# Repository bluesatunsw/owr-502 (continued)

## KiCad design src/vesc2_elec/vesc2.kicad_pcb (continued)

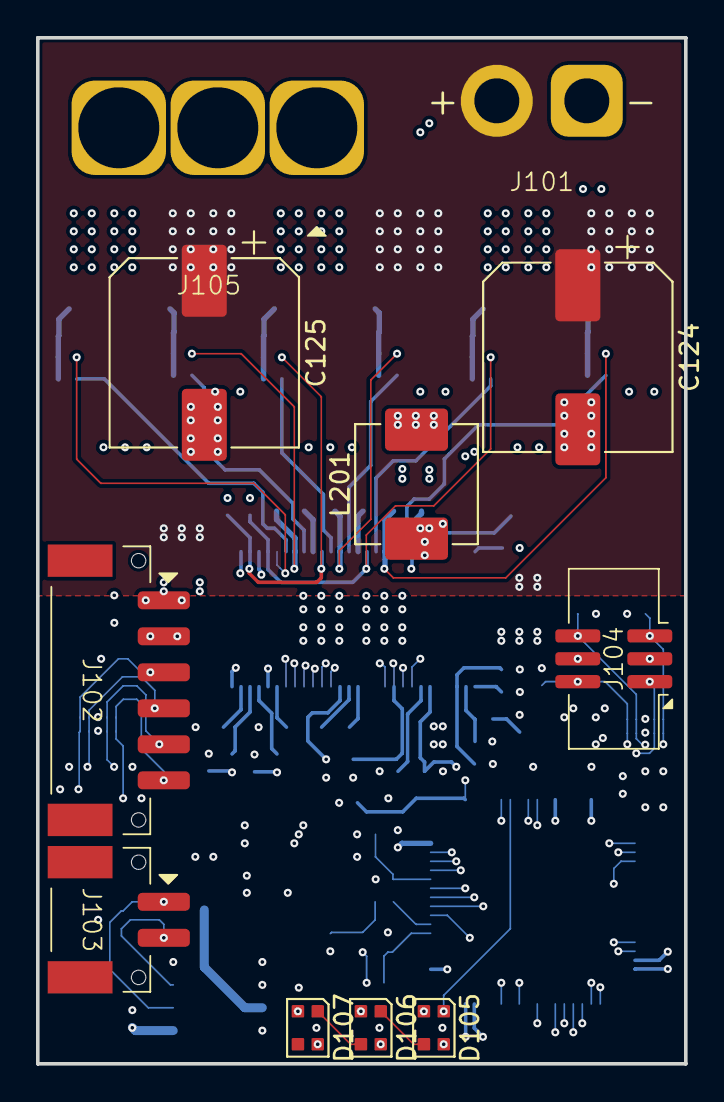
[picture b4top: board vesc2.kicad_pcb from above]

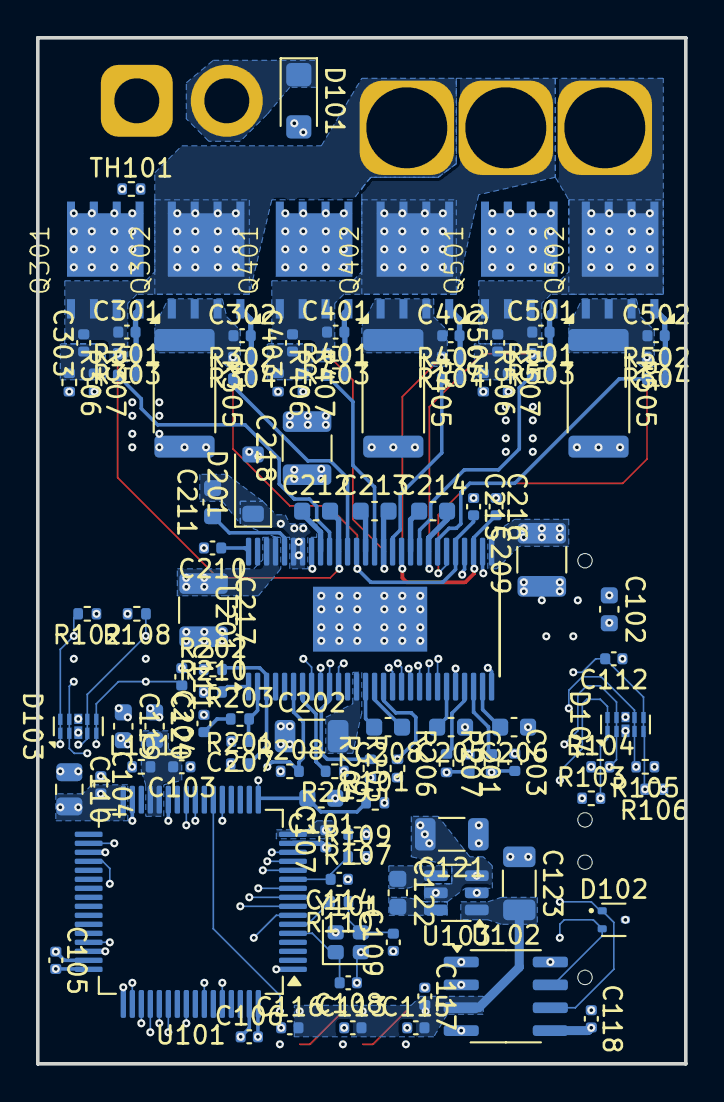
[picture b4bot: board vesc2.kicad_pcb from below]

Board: 6 copper layers, 36.0 x 57.0 mm, 120 parts (109 on the bottom side), 80 nets.

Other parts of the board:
D102: DTVS; SOT-523

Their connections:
/CANH: D102.2; also elsewhere on the board
/CANL: D102.1; also elsewhere on the board
GND: D102.3; also elsewhere on the board

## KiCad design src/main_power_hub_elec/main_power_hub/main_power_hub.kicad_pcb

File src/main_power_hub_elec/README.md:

# Main Power Hub (MPH)

A device which monitors and distributes battery power onto four subcircuits (intended to be either computing power hubs or subsystem power hubs). It complies with the common device specification 2025-04.

Power input from the battery is provided via a male XT90 connector and each of the subcircuits has a female XT60 power output connector.

## Switching
Power to each of the subcircuits can be toggled by the MCU. Triggering the estop, a normally closed contact wired to the device, removes power from all subcircuits bypassing the control of the MCU. The MCU is always powered. As implied by the connector name, each channel is able to output 60A peak and 40A continuous.

Switching on ramps slowly (soft pullup resistor + gate capacitance), switching off is instantaneous.

Power MOSFET: C2902884
https://www.lcsc.com/datasheet/C2902884.pdf

BJT on pullup: BC846s
https://diotec.com/request/datasheet/bc846s.pdf

Gate drive voltage is provided by a charge pump circuit that sums the battery voltage + the 12V rail.
The gate driver is a simple BJT pullup configuration.

Charge pump MOSFET: SSM3K333R
https://toshiba.semicon-storage.com/info/SSM3K333R_datasheet_en_20250220.pdf?did=6736&prodName=SSM3K333R

## Monitoring
The bus voltage is monitored through a voltage divider into an ADC (10k / (10k + 220k)).
The output current of each channel is monitored.
This is done with a 1m shunt resistor on each channel.
The voltage across the resistor is fed into one internal STM32 op-amp per channel.
A compensation capacitor is placed on the output of each op-amp to introduce a pole near 1kHz.
The op-amp pins should be connected internally to the ADCs using software.

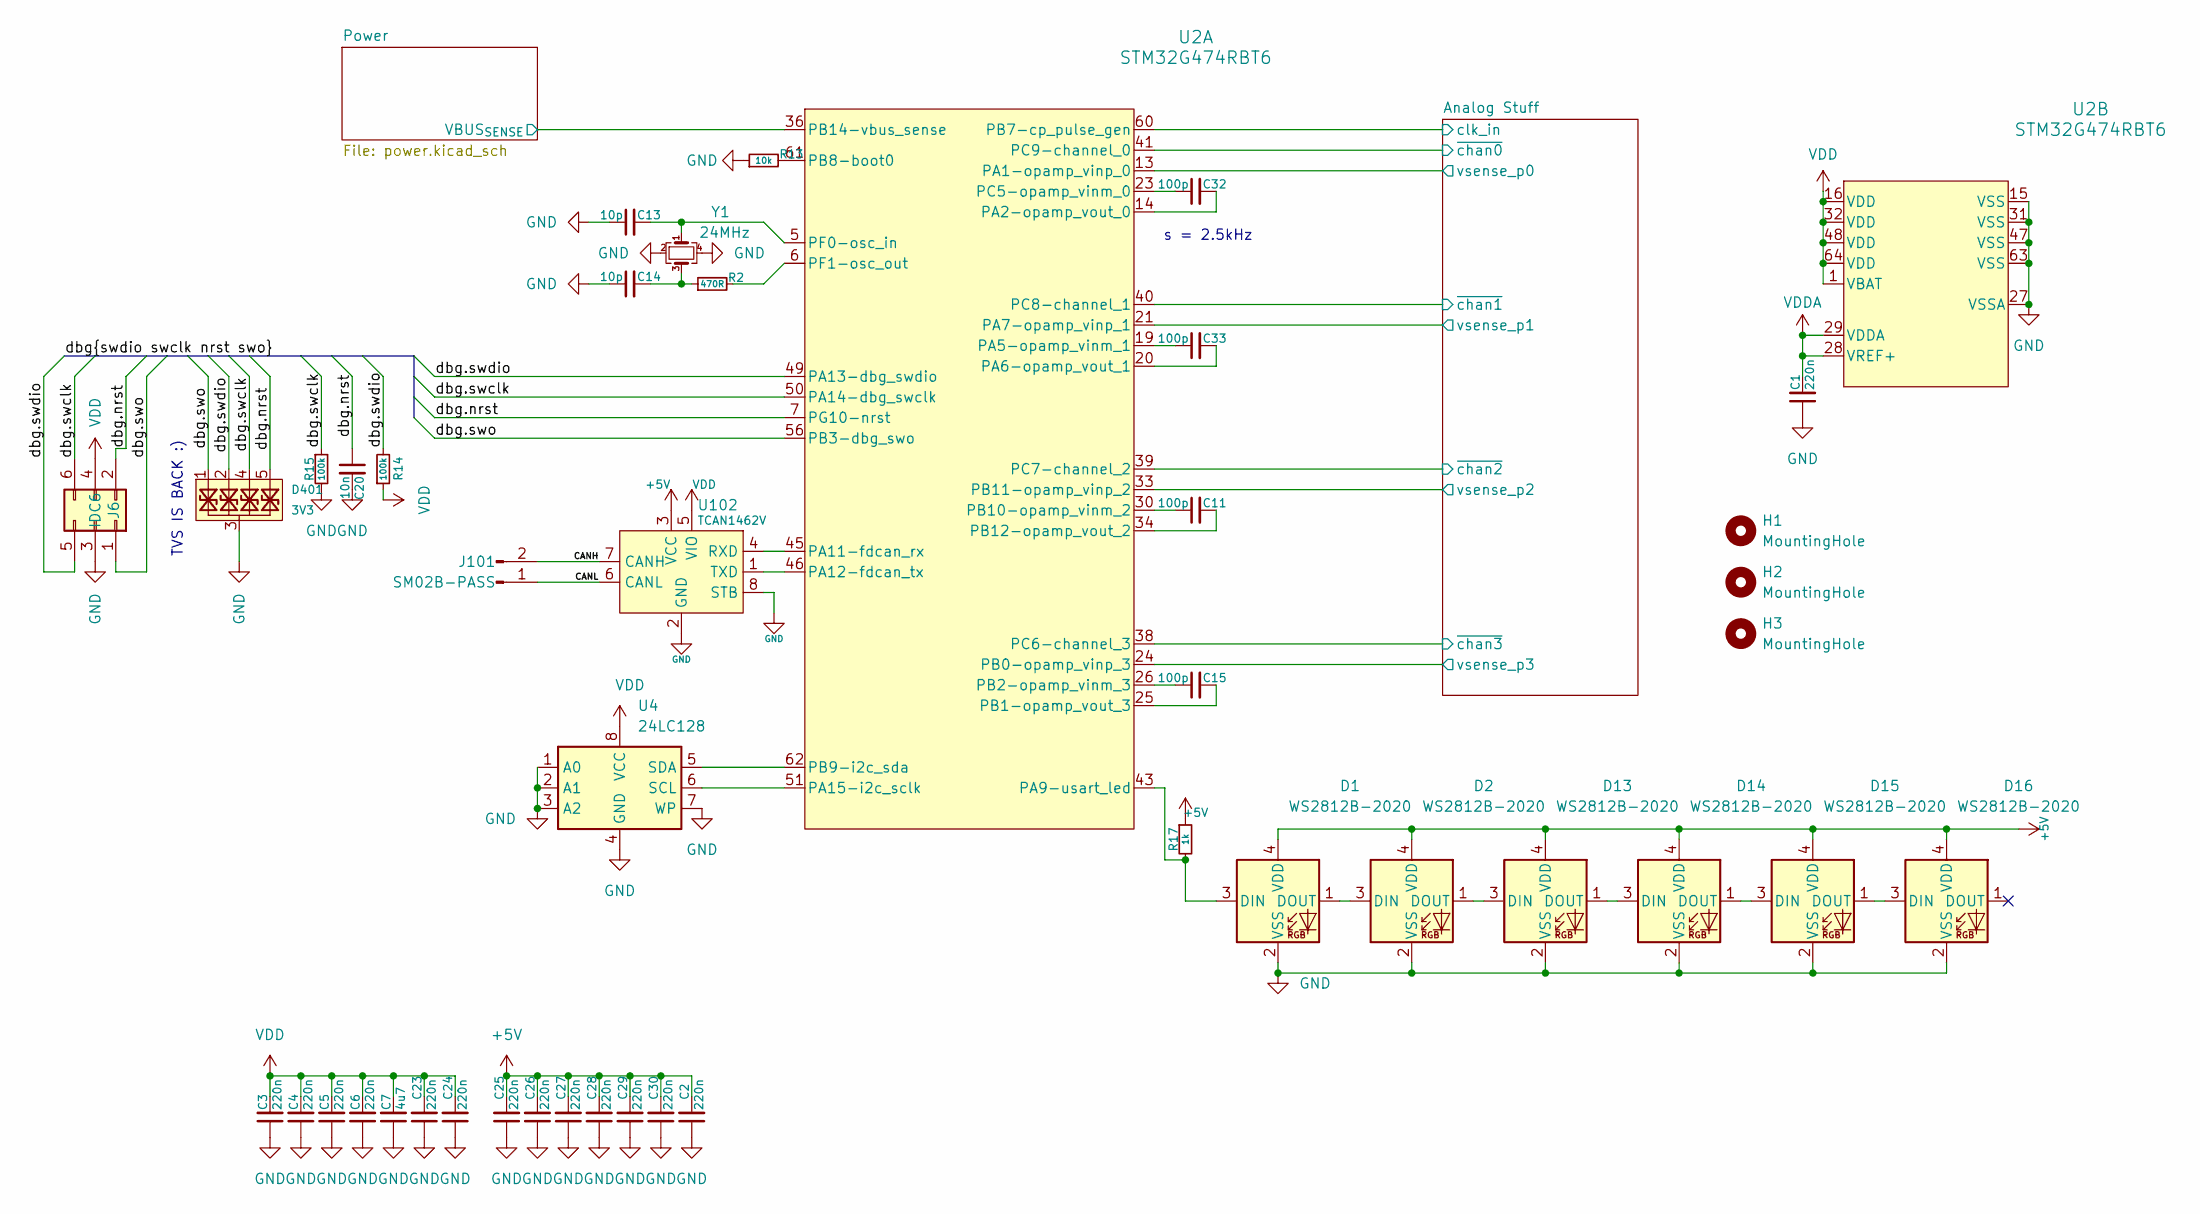
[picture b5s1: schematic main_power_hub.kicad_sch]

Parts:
C1, C2, C3, C4, C5, C6, C23, C24, C25, C26, C27, C28, C29, C30: 220n; C_0402_1005Metric
C7: 4u7; C_0805_2012Metric
C11, C15, C32, C33: 100p; C_0402_1005Metric
C13, C14: 10p; C_0402_1005Metric
C20: 10n; C_0402_1005Metric
D1, D2, D13, D14, D15, D16: WS2812B-2020
D401: 3V3; Diodes_UDFN-10_1x2.5mm_P0.5mm
H1, H2, H3: MountingHole; M2.5_Internal
J6: IDC6
J101: SM02B-PASS
R2: 470R; R_0402_1005Metric
R13: 10k; R_0402_1005Metric
R14, R15: 100k; R_0402_1005Metric
R17: 1k; R_0402_1005Metric
U2: STM32G474RBT6; LQFP-64-0.5
U4: 24LC128; TSSOP-8_4.4x3.0-0.65
U102: TCAN1462V; SOIC-8_3.9x4.9mm_P1.27mm
Y1: 24MHz; Crystal_SMD_2016-4Pin_2.0x1.6mm

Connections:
+5V: C2.2, C25.2, C26.2, C27.2, C28.2, C29.2, C30.2, D1.4 (VDD), D2.4 (VDD), D13.4 (VDD), D14.4 (VDD), D15.4 (VDD), D16.4 (VDD), R17.1, U102.3 (VCC); also elsewhere on the board
/Analog Stuff/clk_in: U2.60 (PB7-cp_pulse_gen); also elsewhere on the board
/Analog Stuff/vsense_p0: U2.13 (PA1-opamp_vinp_0); also elsewhere on the board
/Analog Stuff/vsense_p1: U2.21 (PA7-opamp_vinp_1); also elsewhere on the board
/Analog Stuff/vsense_p2: U2.33 (PB11-opamp_vinp_2); also elsewhere on the board
/Analog Stuff/vsense_p3: U2.24 (PB0-opamp_vinp_3); also elsewhere on the board
/Analog Stuff/~chan0: U2.41 (PC9-channel_0); also elsewhere on the board
/Analog Stuff/~chan1: U2.40 (PC8-channel_1); also elsewhere on the board
/Analog Stuff/~chan2: U2.39 (PC7-channel_2); also elsewhere on the board
/Analog Stuff/~chan3: U2.38 (PC6-channel_3); also elsewhere on the board
/CANH: J101.2, U102.7 (CANH); also elsewhere on the board
/CANL: J101.1, U102.6 (CANL); also elsewhere on the board
/Power/VBUS_{SENSE}: U2.36 (PB14-vbus_sense); also elsewhere on the board
/dbg.nrst: C20.1, D401.5, D401.6, J6.2, U2.7 (PG10-nrst)
/dbg.swclk: D401.4, D401.7, J6.6, R15.1, U2.50 (PA14-dbg_swclk)
/dbg.swdio: D401.2, D401.9, J6.5, R14.2, U2.49 (PA13-dbg_swdio)
/dbg.swo: D401.1, D401.10, J6.1, U2.56 (PB3-dbg_swo)
unnamed: C14.2, R2.1, Y1.3
unnamed: D1.3 (DIN), R17.2, U2.43 (PA9-usart_led)
unnamed: D1.1 (DOUT), D2.3 (DIN)
unnamed: D2.1 (DOUT), D13.3 (DIN)
unnamed: D13.1 (DOUT), D14.3 (DIN)
unnamed: D14.1 (DOUT), D15.3 (DIN)
unnamed: D15.1 (DOUT), D16.3 (DIN)
unnamed: C32.2, U2.14 (PA2-opamp_vout_0)
unnamed: C33.1, U2.19 (PA5-opamp_vinm_1)
unnamed: C33.2, U2.20 (PA6-opamp_vout_1)
unnamed: U2.51 (PA15-i2c_sclk), U4.6 (SCL)
unnamed: C15.2, U2.25 (PB1-opamp_vout_3)
unnamed: C15.1, U2.26 (PB2-opamp_vinm_3)
unnamed: R13.2, U2.61 (PB8-boot0)
unnamed: U2.62 (PB9-i2c_sda), U4.5 (SDA)
unnamed: C11.1, U2.30 (PB10-opamp_vinm_2)
unnamed: C11.2, U2.34 (PB12-opamp_vout_2)
unnamed: C32.1, U2.23 (PC5-opamp_vinm_0)
unnamed: C13.2, U2.5 (PF0-osc_in), Y1.1
unnamed: R2.2, U2.6 (PF1-osc_out)
unnamed: U2.45 (PA11-fdcan_rx), U102.4 (RXD)
unnamed: U2.46 (PA12-fdcan_tx), U102.1 (TXD)
VDD: C3.2, C4.2, C5.2, C6.2, C7.2, C23.2, C24.2, J6.4, R14.1, U2.1 (VBAT), U2.16 (VDD), U2.32 (VDD), U2.48 (VDD), U2.64 (VDD), U4.8 (VCC), U102.5 (VIO); also elsewhere on the board
VDDA: C1.2, U2.28 (VREF+), U2.29 (VDDA); also elsewhere on the board

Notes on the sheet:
s = 2.5kHz
TVS IS BACK :)

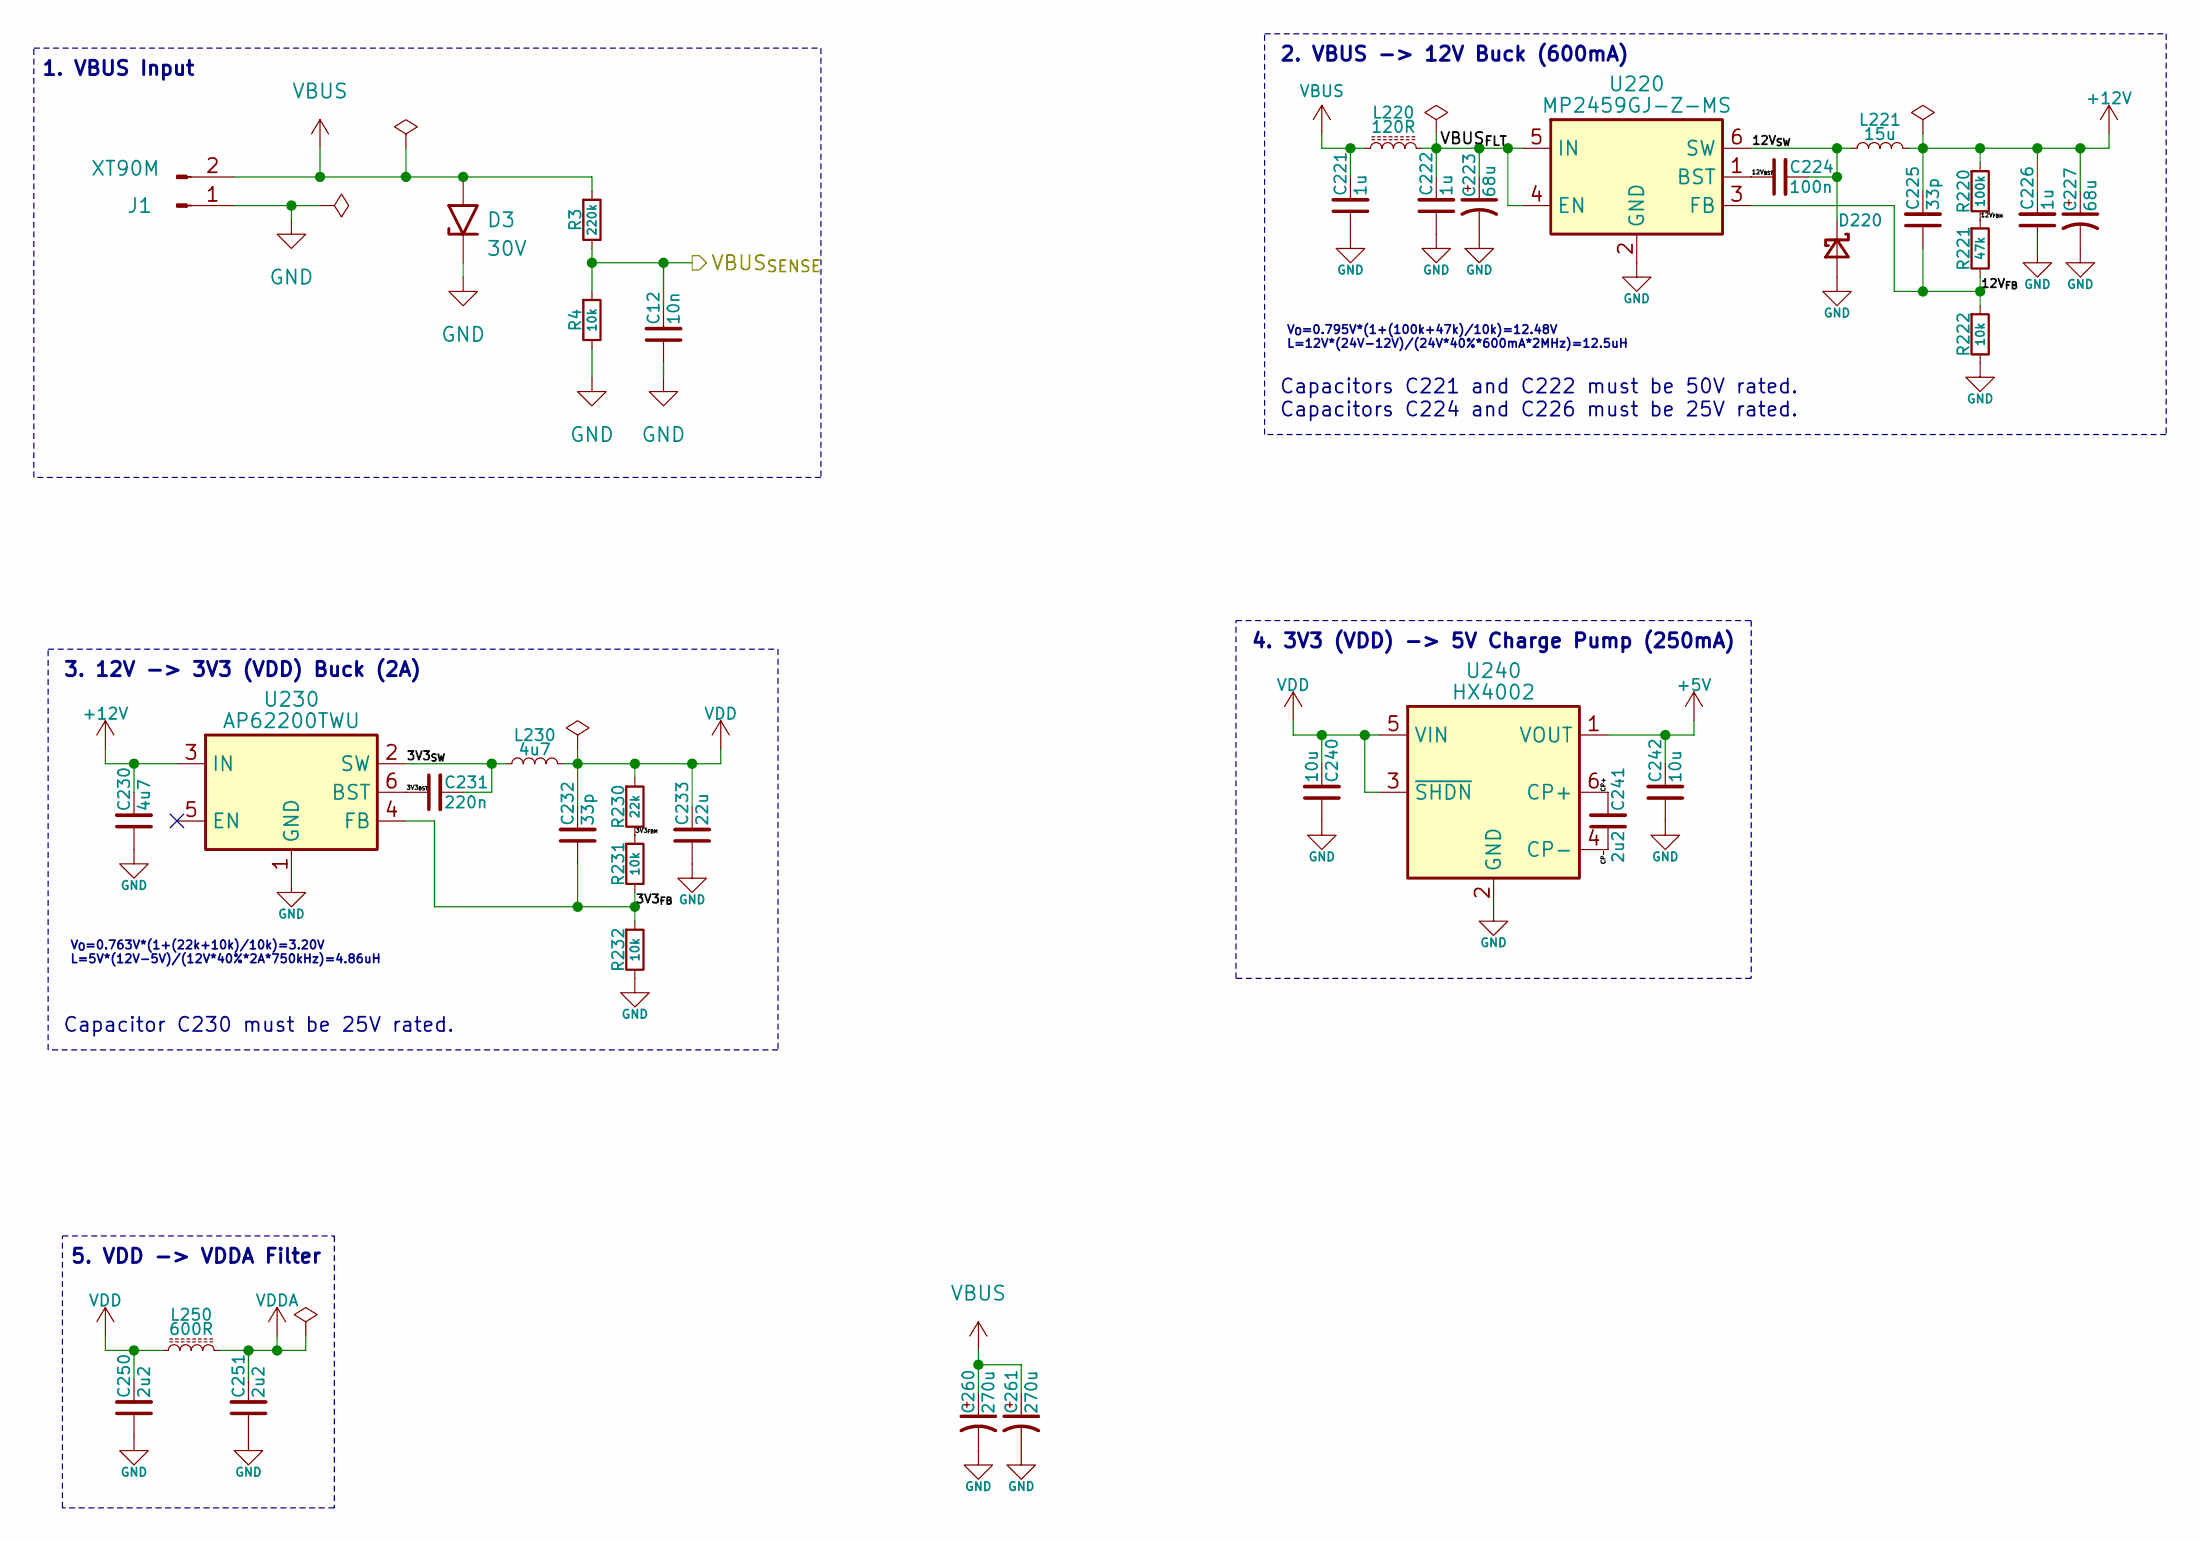
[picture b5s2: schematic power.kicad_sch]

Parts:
C12: 10n; C_0402_1005Metric
C221, C222: 1u; C_1206_3216Metric
C223, C227: 68u; CP_Elec_6.3x7.7
C224: 100n; C_0402_1005Metric
C225, C232: 33p; C_0402_1005Metric
C226: 1u; C_0805_2012Metric
C230: 4u7; C_1206_3216Metric
C231: 220n; C_0402_1005Metric
C233: 22u; C_1210_3225Metric
C240, C242: 10u; C_1206_3216Metric
C241, C250, C251: 2u2; C_0603_1608Metric
C260, C261: 270u; CP_Elec_10x10
D3: 30V; D_SMF
D220: D_Schottky_Small; D_SOD-123
J1: XT90M; AMASS_XT90PW-M_1x02_P10.90mm_Horizontal
L220: 120R; R_0603_1608Metric
L221: 15u; L_Changjiang_FNR5040S
L230: 4u7; L_Changjiang_FNR4020S
L250: 600R; R_0402_1005Metric
R3: 220k; R_0402_1005Metric
R4, R222, R231, R232: 10k; R_0402_1005Metric
R220: 100k; R_0402_1005Metric
R221: 47k; R_0402_1005Metric
R230: 22k; R_0402_1005Metric
U220: MP2459GJ-Z-MS; TSOT-23-6
U230: AP62200TWU; TSOT-23-6
U240: HX4002; SOT-23-6

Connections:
+5V: C242.2, U240.1 (VOUT); also elsewhere on the board
+12V: C225.2, C226.2, C227.1, C230.2, L221.1, R220.1, U230.3 (IN); also elsewhere on the board
/Power/3V3_{BST}: C231.1, U230.6 (BST)
/Power/3V3_{FBM}: R230.2, R231.1
/Power/3V3_{FB}: C232.1, R231.2, R232.1, U230.4 (FB)
/Power/3V3_{SW}: C231.2, L230.1, U230.2 (SW)
/Power/12V_{BST}: C224.1, U220.1 (BST)
/Power/12V_{FBM}: R220.2, R221.1
/Power/12V_{FB}: C225.1, R221.2, R222.1, U220.3 (FB)
/Power/12V_{SW}: C224.2, D220.1 (K), L221.2, U220.6 (SW)
/Power/CP+: C241.2, U240.6 (CP+)
/Power/CP-: C241.1, U240.4 (CP-)
/Power/VBUS_{FLT}: C222.2, C223.1, L220.2, U220.4 (EN), U220.5 (IN)
/Power/VBUS_{SENSE}: C12.2, R3.2, R4.1; also elsewhere on the board
VBUS: C221.2, C260.1, C261.1, D3.2 (A2), J1.2, L220.1, R3.1; also elsewhere on the board
VDD: C232.2, C233.2, C240.2, C250.2, L230.2, L250.1, R230.1, U240.3 (~SHDN), U240.5 (VIN); also elsewhere on the board
VDDA: C251.2, L250.2; also elsewhere on the board

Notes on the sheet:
4. 3V3 (VDD) -> 5V Charge Pump (250mA)
Capacitor C230 must be 25V rated.
1. VBUS Input
V_{O}=0.795V*(1+(100k+47k)/10k)=12.48V L=12V*(24V-12V)/(24V*40%*600mA*2MHz)=12.5uH
Capacitors C221 and C222 must be 50V rated. Capacitors C224 and C226 must be 25V rated.
2. VBUS -> 12V Buck (600mA)
5. VDD -> VDDA Filter
3. 12V -> 3V3 (VDD) Buck (2A)
V_{O}=0.763V*(1+(22k+10k)/10k)=3.20V L=5V*(12V-5V)/(12V*40%*2A*750kHz)=4.86uH

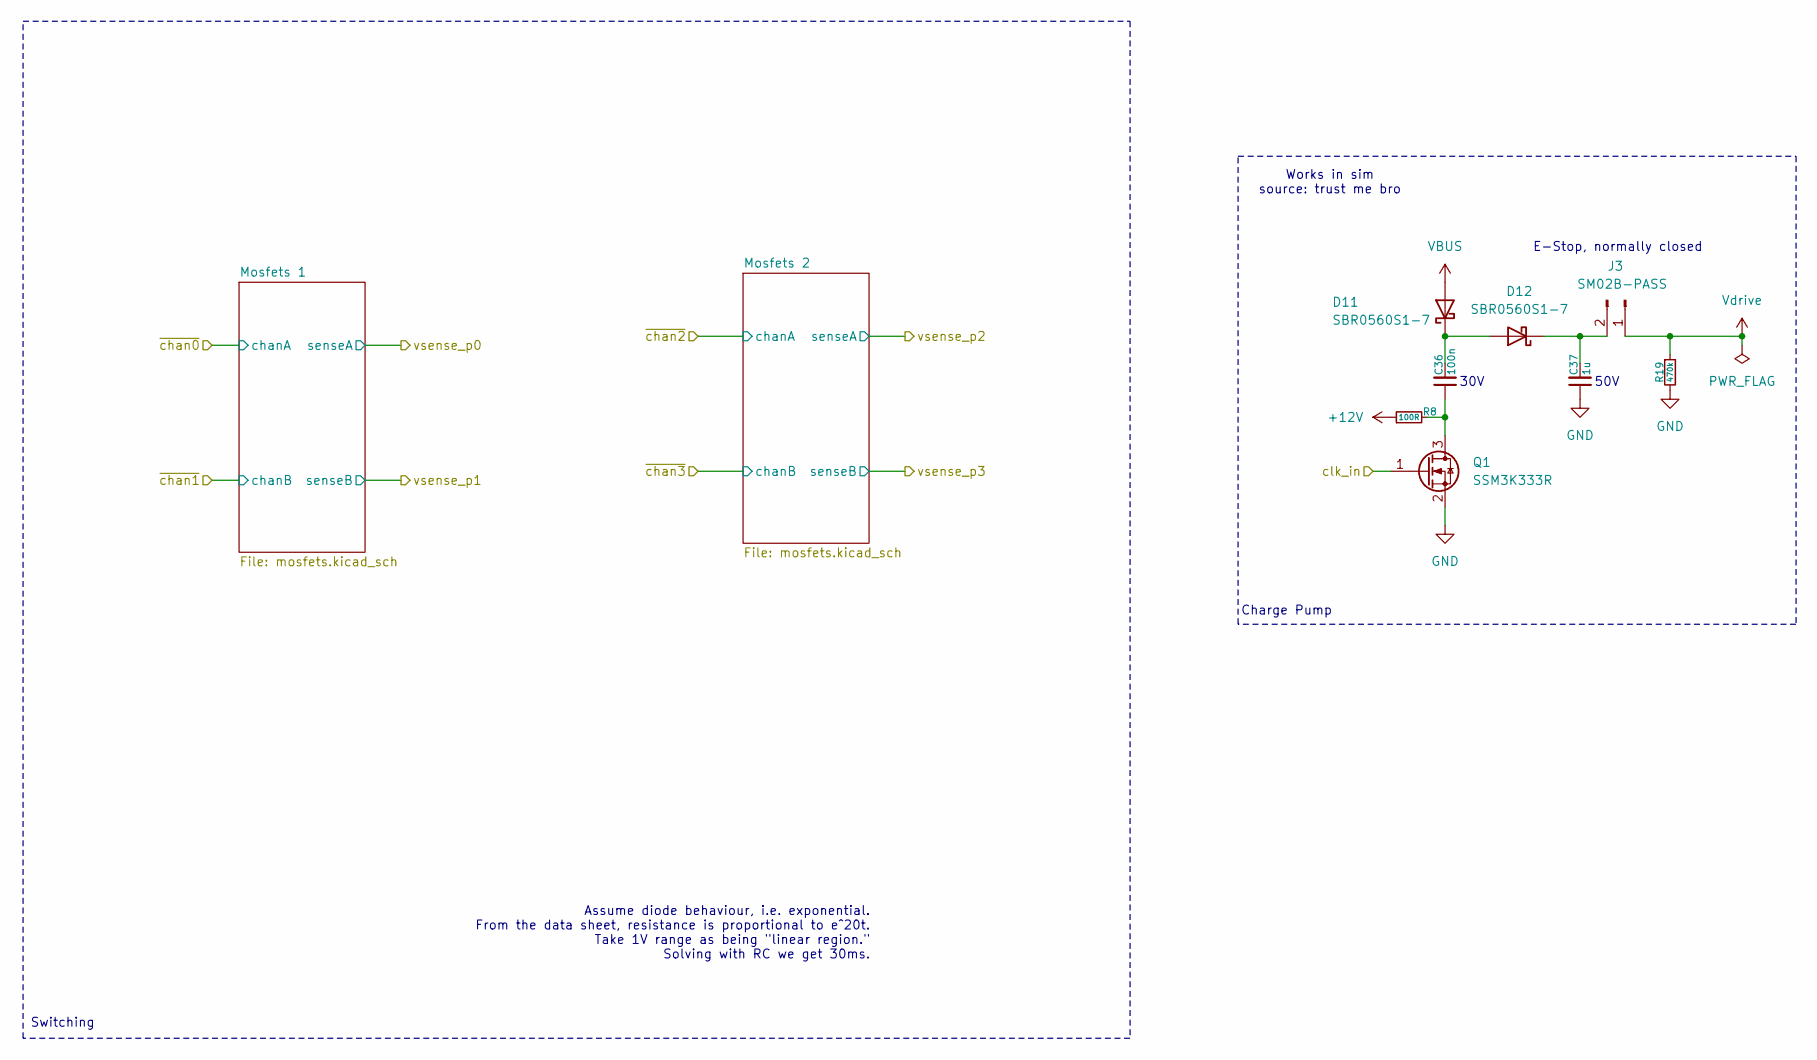
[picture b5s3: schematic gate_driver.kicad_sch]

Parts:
C36: 100n; C_0603_1608Metric
C37: 1u; C_1206_3216Metric
D11, D12: SBR0560S1-7; D_SOD-123
J3: SM02B-PASS
Q1: SSM3K333R; SOT-23-3
R8: 100R; R_0402_1005Metric
R19: 470k; R_0402_1005Metric

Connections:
+12V: R8.1; also elsewhere on the board
/Analog Stuff/clk_in: Q1.1 (G); also elsewhere on the board
unnamed: C36.2, D11.1 (K), D12.2 (A)
unnamed: C37.2, D12.1 (K), J3.2
unnamed: C36.1, Q1.3 (D), R8.2
VBUS: D11.2 (A); also elsewhere on the board
Vdrive: J3.1, R19.1; also elsewhere on the board

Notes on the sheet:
Switching
Charge Pump
50V
E-Stop, normally closed
Assume diode behaviour, i.e. exponential. From the data sheet, resistance is proportional to e^20t. Take 1V range as being "linear region." Solving with RC we get 30ms.
Works in sim source: trust me bro
30V

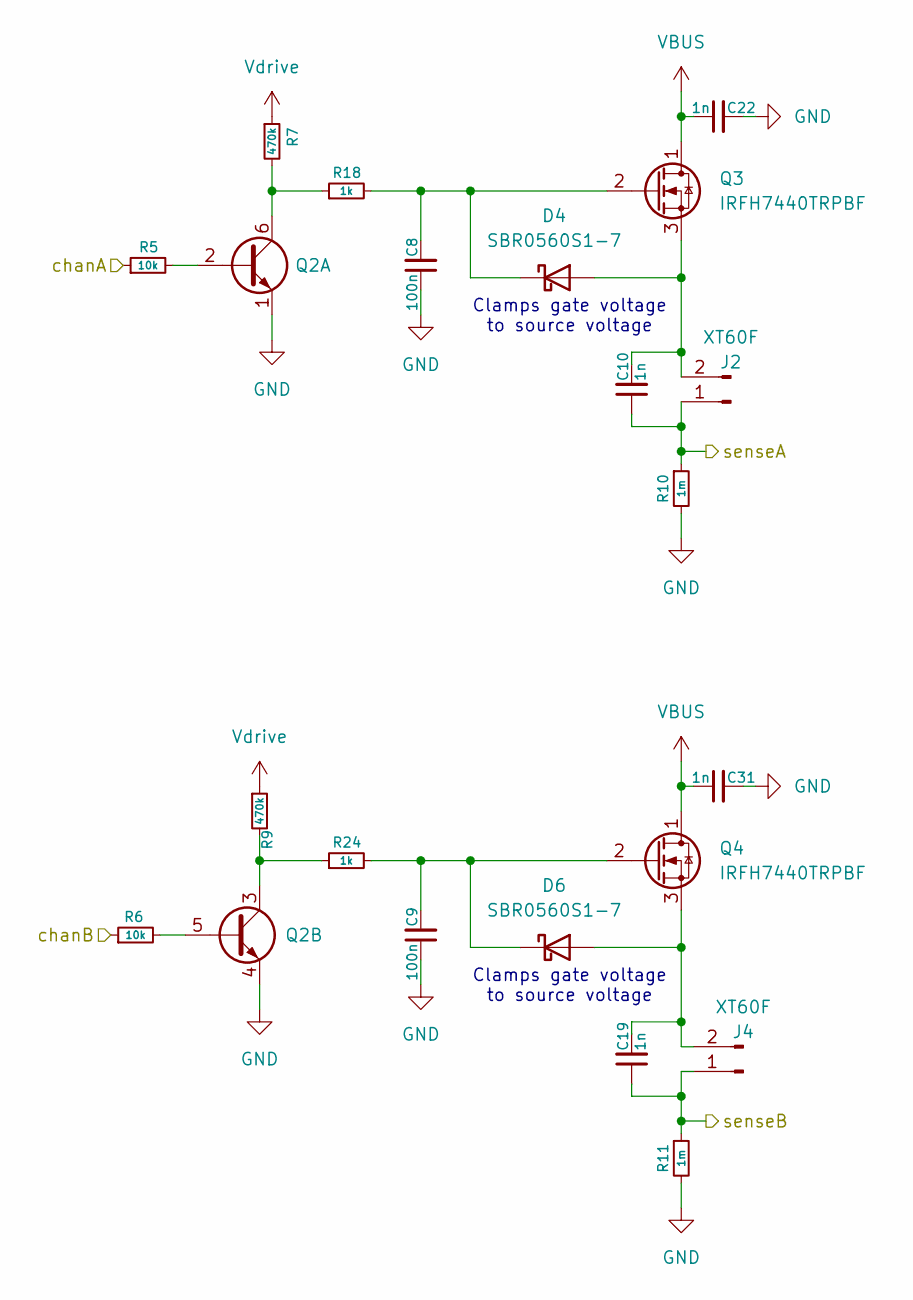
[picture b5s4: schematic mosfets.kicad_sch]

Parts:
C8, C9: 100n; C_0603_1608Metric
C10, C19, C22, C31: 1n; C_0402_1005Metric
D4, D6: SBR0560S1-7; D_SOD-123
J2, J4: XT60F; AMASS_XT60PW-F_1x02_P7.20mm_Horizontal
Q2: Q_Dual_NPN_NPN_E1B1C2E2B2C1; SOT-363
Q3, Q4: IRFH7440TRPBF; PQFN_5x6mm_E_DGS
R5, R6: 10k; R_0402_1005Metric
R7, R9: 470k; R_0402_1005Metric
R10, R11: 1m; R_2512_6332Metric
R18, R24: 1k; R_0402_1005Metric

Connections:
/Analog Stuff/vsense_p2: C10.1, J2.1, R10.1; also elsewhere on the board
/Analog Stuff/vsense_p3: C19.1, J4.1, R11.1; also elsewhere on the board
/Analog Stuff/~chan2: R5.1; also elsewhere on the board
/Analog Stuff/~chan3: R6.1; also elsewhere on the board
unnamed: C8.2, D4.1 (K), Q3.2 (G), R18.2
unnamed: C9.2, D6.1 (K), Q4.2 (G), R24.2
unnamed 38: Q2.6 (C1), R7.2, R18.1; also elsewhere on the board
unnamed 40: Q2.3 (C2), R9.2, R24.1; also elsewhere on the board
unnamed: Q2.2 (B1), R5.2
unnamed: Q2.5 (B2), R6.2
VBUS: C22.1, C31.1, Q3.1 (D), Q4.1 (D); also elsewhere on the board
Vdrive: R7.1, R9.1; also elsewhere on the board

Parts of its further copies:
C42, C43: 100n; C_0603_1608Metric
C44, C46, C48, C49: 1n; C_0402_1005Metric
J8, J9: XT60F; AMASS_XT60PW-F_1x02_P7.20mm_Horizontal
Q8: Q_Dual_NPN_NPN_E1B1C2E2B2C1; SOT-363
Q9, Q10: IRFH7440TRPBF; PQFN_5x6mm_E_DGS
R16, R21: 10k; R_0402_1005Metric
R20, R25: 1k; R_0402_1005Metric
R22, R23: 470k; R_0402_1005Metric
R26, R27: 1m; R_2512_6332Metric

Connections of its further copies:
/Analog Stuff/vsense_p0: C44.1, J8.1, R26.1; also elsewhere on the board
/Analog Stuff/vsense_p1: C46.1, J9.1, R27.1; also elsewhere on the board
/Analog Stuff/~chan0: R16.1; also elsewhere on the board
/Analog Stuff/~chan1: R21.1; also elsewhere on the board
unnamed 33: C42.1, C44.2, J8.2, Q9.3 (S); also elsewhere on the board
unnamed 34: C42.2, Q9.2 (G), R20.2; also elsewhere on the board
unnamed 36: C43.1, C46.2, J9.2, Q10.3 (S); also elsewhere on the board
unnamed 37: C43.2, Q10.2 (G), R25.2; also elsewhere on the board
unnamed 39: Q8.6 (C1), R20.1, R22.2; also elsewhere on the board
unnamed 47: Q8.3 (C2), R23.2, R25.1; also elsewhere on the board
unnamed: Q8.2 (B1), R16.2
unnamed: Q8.5 (B2), R21.2
VBUS: C48.1, C49.1, Q9.1 (D), Q10.1 (D); also elsewhere on the board
Vdrive: R22.1, R23.1; also elsewhere on the board

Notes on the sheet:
Clamps gate voltage to source voltage

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
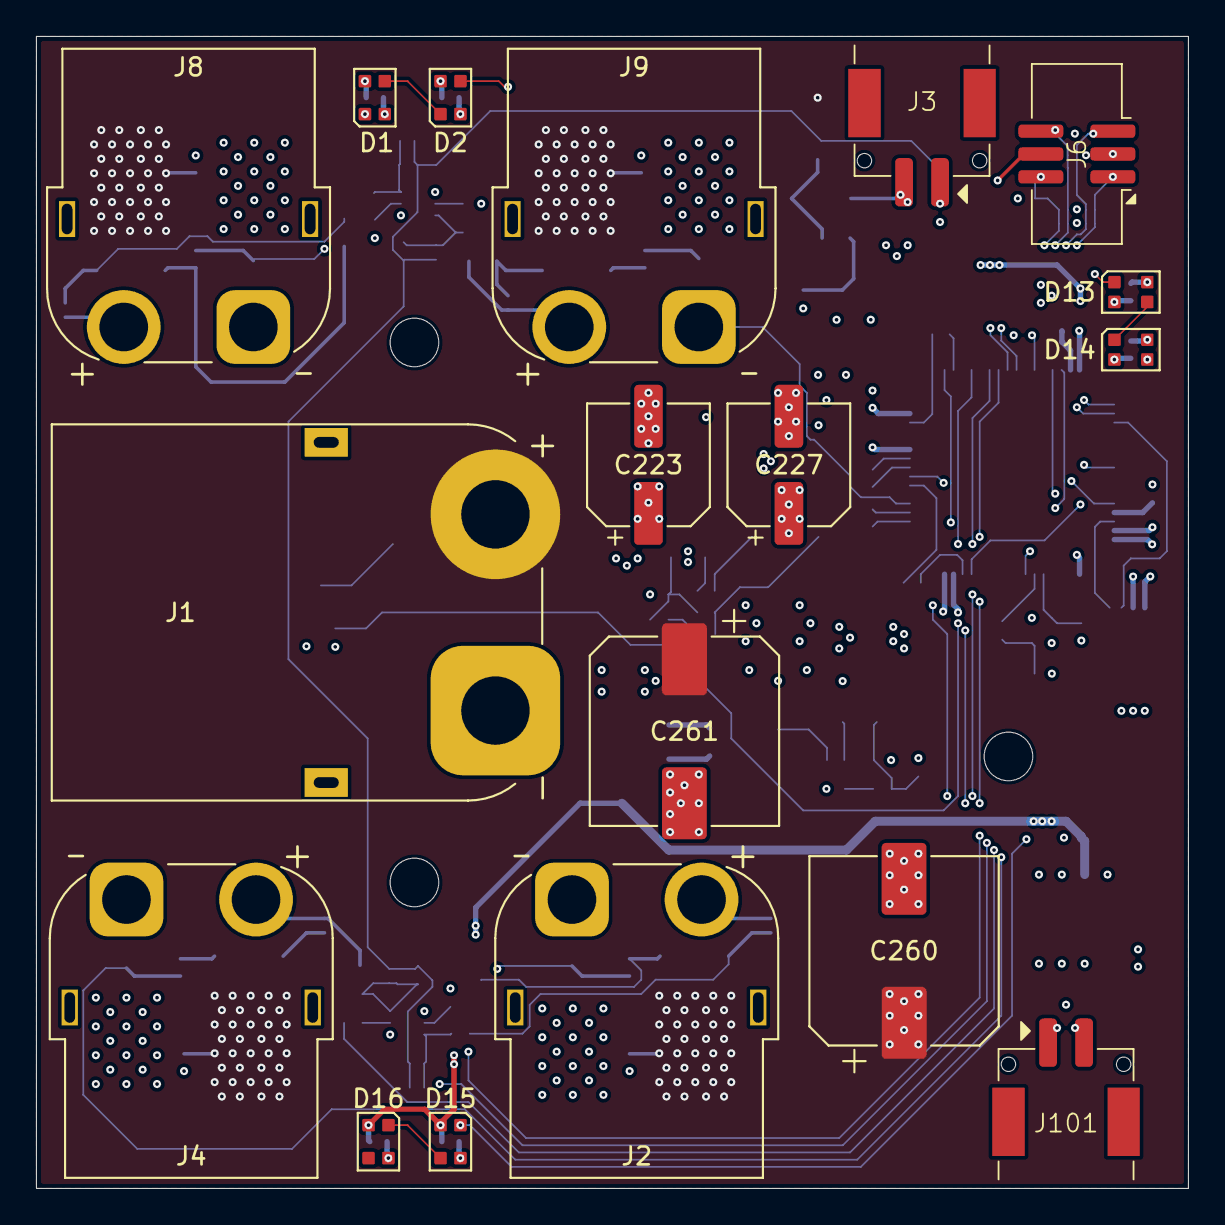
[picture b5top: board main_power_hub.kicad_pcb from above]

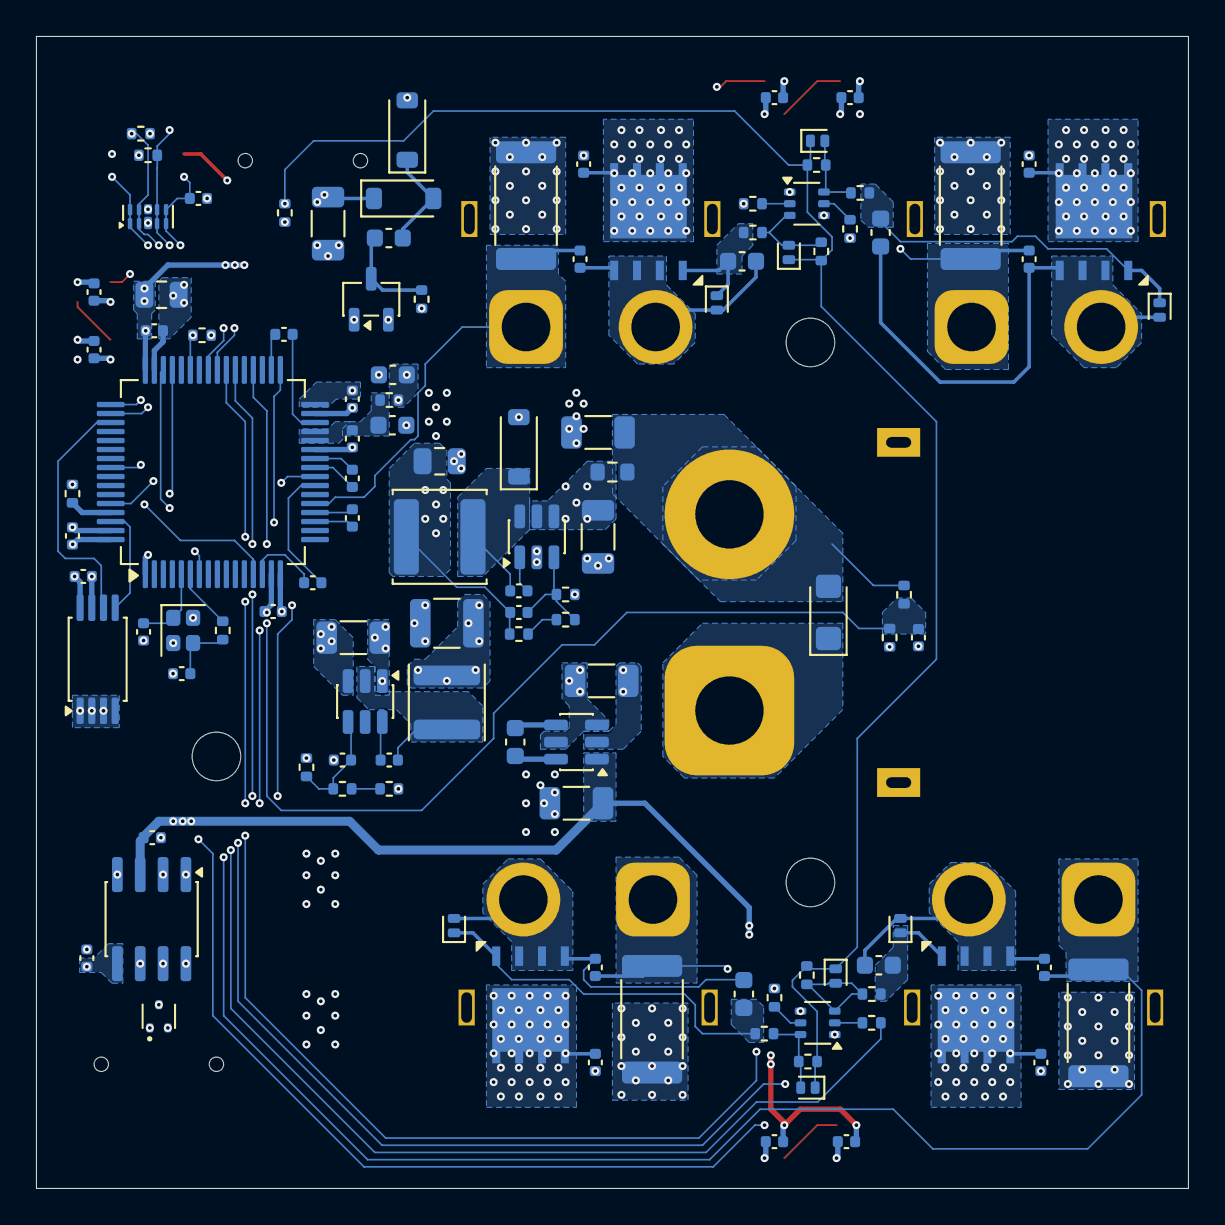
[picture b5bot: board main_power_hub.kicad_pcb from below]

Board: 6 copper layers, 64.0 x 64.0 mm, 135 parts (114 on the bottom side), 75 nets.

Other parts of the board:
D5, D7, D8, D9, D10, D17: SBR0240LP-7; D_SOD-882D
D101: 5V; SOT-523

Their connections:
/CANH: D101.1; also elsewhere on the board
/CANL: D101.2; also elsewhere on the board
unnamed 33: D5.2 (A); also elsewhere on the board
unnamed 34: D5.1 (K); also elsewhere on the board
unnamed 36: D7.2 (A); also elsewhere on the board
unnamed 37: D7.1 (K); also elsewhere on the board
unnamed 38: D8.2 (A); also elsewhere on the board
unnamed 39: D9.2 (A); also elsewhere on the board
unnamed 40: D10.2 (A); also elsewhere on the board
unnamed 47: D17.2 (A); also elsewhere on the board
Vdrive: D8.1 (K), D9.1 (K), D10.1 (K), D17.1 (K); also elsewhere on the board
